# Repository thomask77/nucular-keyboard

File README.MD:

Toolchain
=========
  * gcc-arm-embedded toolchain >= 4.9-2014-q4
    * https://launchpad.net/gcc-arm-embedded

  * Other tools (use cygwin for windows)
    * python2
    * make

  * Initial flash programming
    * STM32 ST-LINK utility (windows)
    * https://github.com/texane/stlink (linux)

  * Flash programming with DFU bootloader
    * STM32 DfuSe utility (windows)
    * Openmoko dfu-util (linux)

Building
========
```bash
make boot    # Build USB DFU bootloader
make all     # Build actual keyboard application
```

Initial flash programming
=========================
Unfortunately, the STM32L052 does not have a built-in USB bootloader. So the
initial programming has to be done using a SWD adapter. A cheap STM32 discovery
board will do fine.

Windows
-------
Use the ST-LINK utility to flash `obj_boot/f00b00t.hex` and
`obj_app/nucular_kb.hex`.
   
Hint: You can also copy the ST-LINK utility to Tools/st-link and use `make`
to do the flashing:

```bash
make boot_flash
make flash
```

Linux
-----
Use Texane's stlink utility to do the flashing:

```bash
sudo st-flash --reset write obj_boot/f00b00t.bin 0x08000000
sudo st-flash --reset write obj_app/drquad.bin 0x08010000
```

Hint: Read the st-flash documentation and install udev rules
to flash without root privileges.

Flash programming with DFU bootloader
=====================================
After the USB DFU bootloader has been flashed, the application can be updated
without any external tools. Press FN+POWER on your keyboard to enter the DFU-
bootloader mode.

Windows
-------
Use ST's DfuSe Application to flash `obj_app/nucular_kb.dfu`

Linux
-----
Use Openmoko's dfu-util to flash the application:

```bash
sudo dfu-util -D obj_app/nucular_kb.dfu
```

printf()-Debugging
==================
The application uses a generic HID endpoint to print debug messages. This
endpoint is fully compatible with PJRC's [hid_listen] 
(https://www.pjrc.com/teensy/hid_listen.html) program.

The program (source and binaries) is included in the Tools directory.

Eclipse settings
================
  * Download and configure Eclipse Luna:
    * Help -> Install new Software -> Add
      * Name: `http://pydev.org/updates`
      * Location: `http://pydev.org/updates`
    * Install the following plugins:
      * Programming Languages
        * C/C++ Development Tools
      * Mobile and Device Development
        * C/C++ GCC Cross Compiler Support
        * C/C++ GDB Hardware Debugging
     * PyDev
        * PyDev for Eclipse
      * Collaboration
        * Eclipse Git Team Provider

  * Window -> Preferences
    * C/C++
      * Build -> Console -> Limit console output: `5000`
      * Editor -> Scalability -> .. number of lines: `50000`
      * Editor -> Folding -> Enable folding of preprocessor branches
      * Code Style -> Formatter -> Import: `Docs/Codestyle.xml`
      * Code Analysis -> Uncheck all options
    * General -> Editors -> Text Editors -> Spelling -> Disable spell checking

Import Project
--------------
  * File -> New -> Makefile Project with Existing Code
    -> Toolchain for Indexer Settigns: Cross GCC

  * Project -> Uncheck "Build Automatically" 
  
  * Project -> Properties -> C/C++ General
    * Preprocessor Include Paths, Macros, etc. -> Providers
      * CDT GCC Build Output Parser: `arm-none-eabi-gcc`
      * CDT Cross GCC Built-in Compiler Settings: `arm-none-eabi-gcc -E -P -v -dD "${INPUTS}"`

  * Make Target Window, Right Click -> New...
    * Target-name: `all -j8`
    * Target-name: `clean`

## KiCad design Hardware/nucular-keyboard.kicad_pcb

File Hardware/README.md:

**KICAD BRANCH -- WORK IN PROGRESS**

**EXPECT FREQUENT REBASES**

# Hardware

# Software

  * KiCad nightly
  * FreeCAD v0.17_pre

# Credits
  * 3D Models for AA01B-S040VA1 and T60 Keyboard by Cong Nguyen, Licensed under
    [CC-BY](http://creativecommons.org/licenses/by/4.0/) License:
    * https://grabcad.com/library/aa01b-s040va1-model-1
    * https://grabcad.com/library/thinkpad-t60-keyboard-with-trackpoint-1

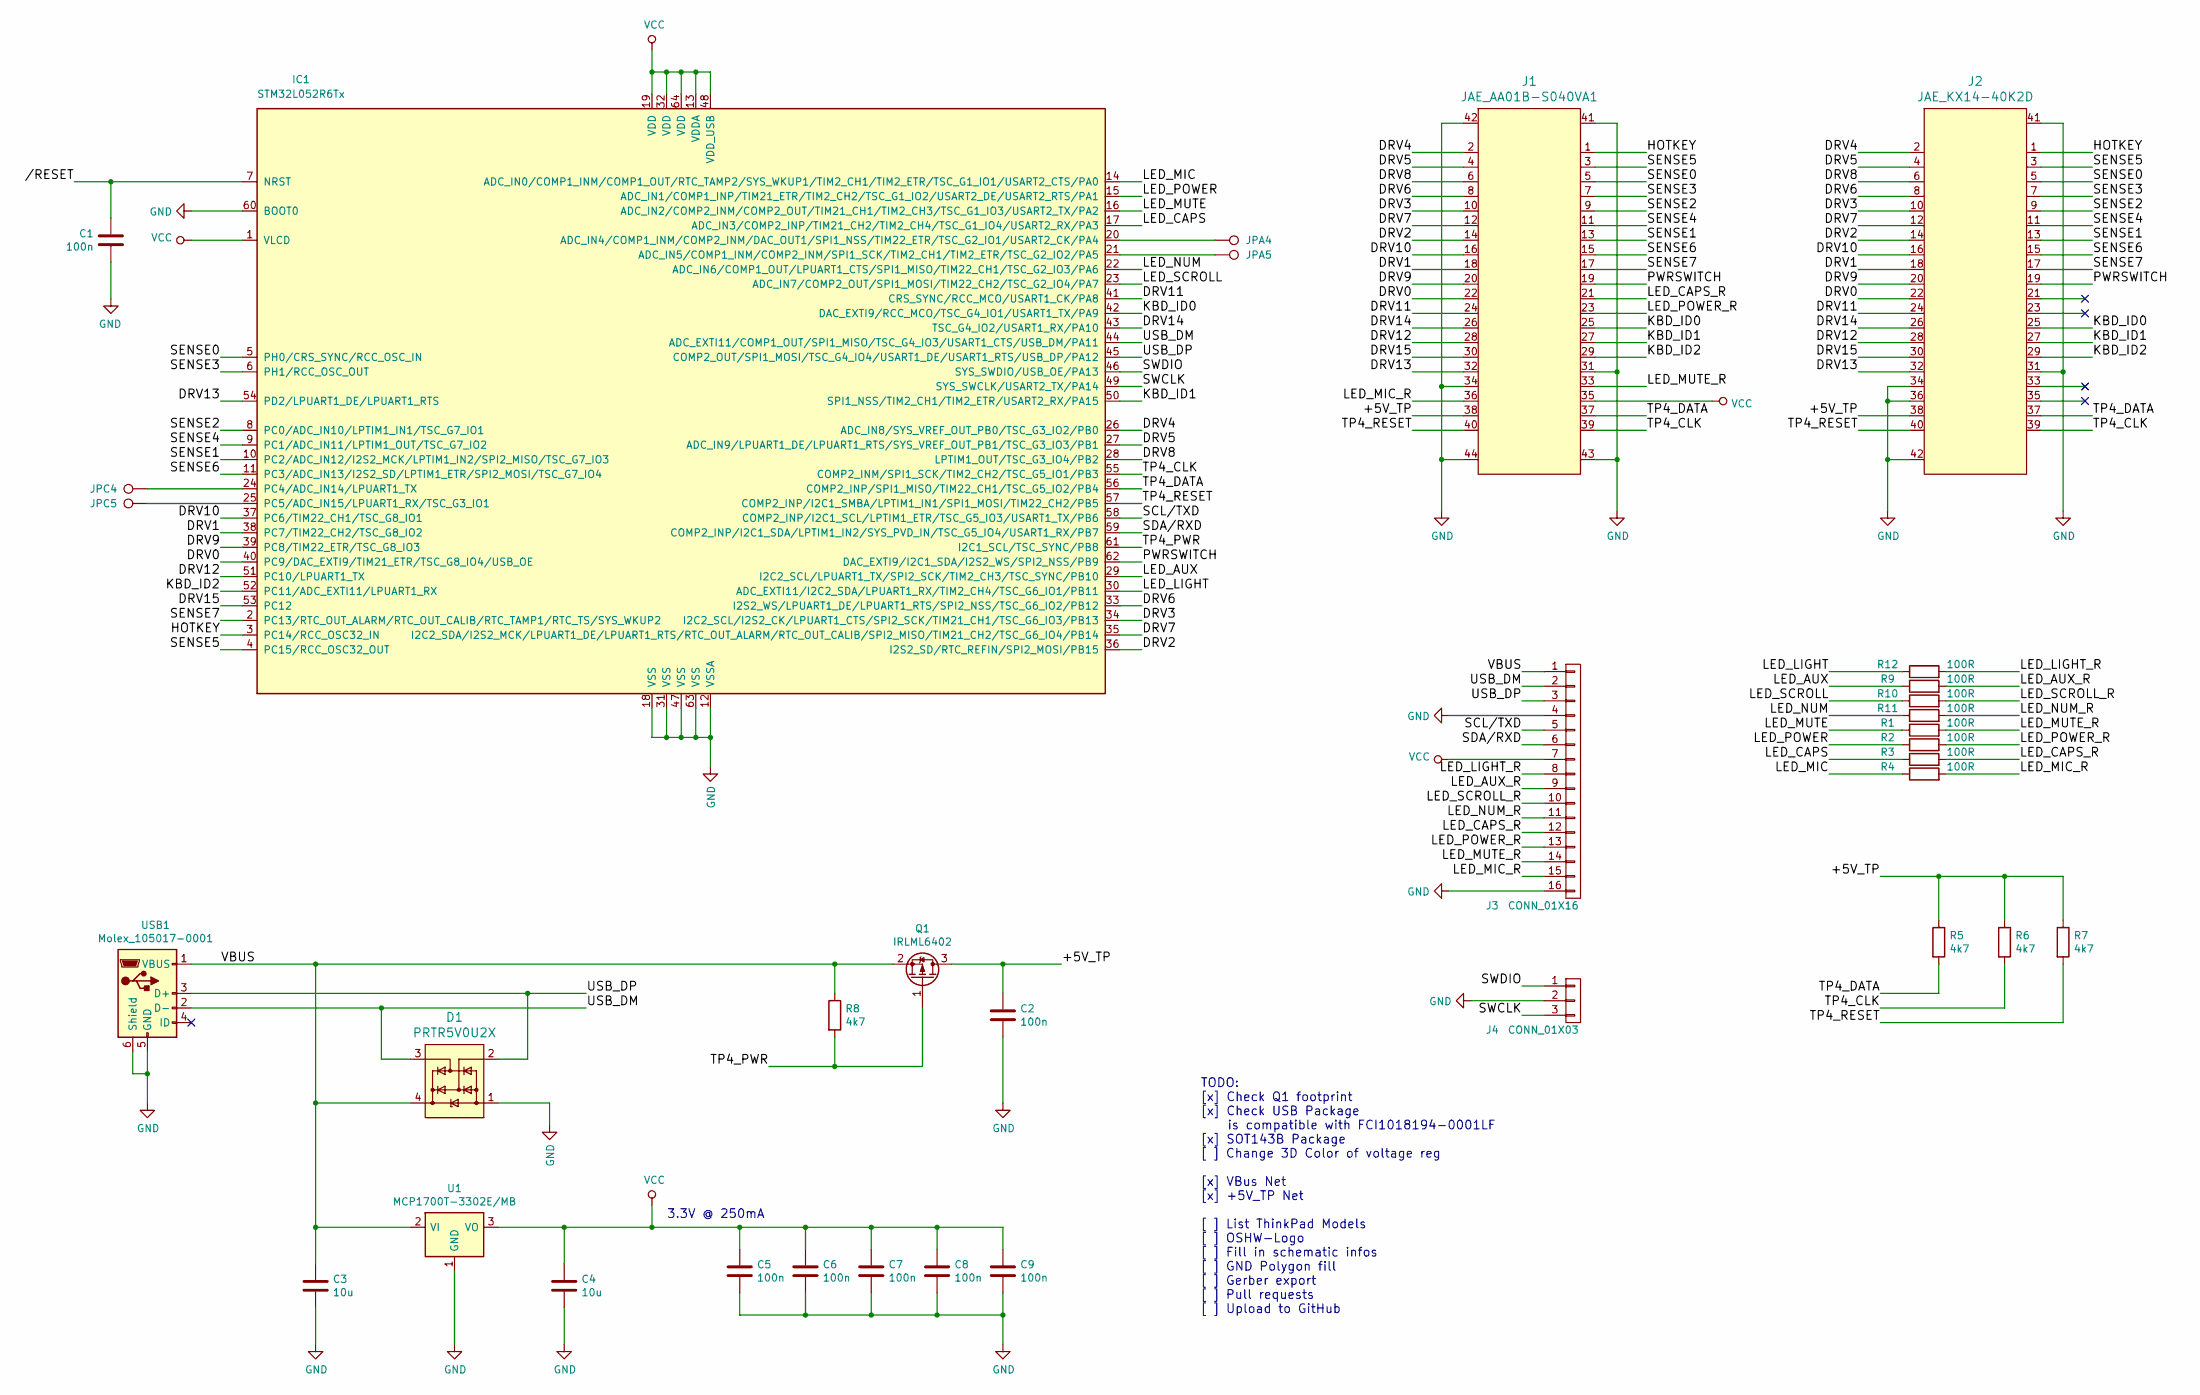
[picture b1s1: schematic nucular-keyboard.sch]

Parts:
C1, C2, C5, C6, C7, C8, C9: 100n; C_0402
C3, C4: 10u; C_0603
D1: PRTR5V0U2X; SOT143B
IC1: STM32L052R6Tx; LQFP-64_10x10mm_Pitch0.5mm
J1: JAE_AA01B-S040VA1
J2: JAE_KX14-40K2D
J3: CONN_01X16; Pin_Header_Straight_1x16_Pitch2.54mm
J4: CONN_01X03; Pin_Header_Straight_1x03_Pitch2.54mm
JPA4, JPA5: TEST_1P; SolderWirePad_single_0-8mmDrill
JPC4, JPC5: TEST_1P; SolderWirePad_single_0-8mmDrill
Q1: IRLML6402; SOT-23
R1, R2, R3, R4, R9, R10, R11, R12: 100R; R_0402
R5, R6, R7, R8: 4k7; R_0402
U1: MCP1700T-3302E/MB; SOT89-3
USB1: Molex_105017-0001; Molex_105017-0001_USB-Micro-B

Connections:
/+5V_TP: C2.1, J1.38, J2.38, Q1.3 (D), R5.1, R6.1, R7.1
//RESET: C1.1, IC1.7 (NRST)
/DRV0: IC1.40 (PC9/DAC_EXTI9/TIM21_ETR/TSC_G8_IO4/USB_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), J1.22, J2.22
/DRV1: IC1.38 (PC7/TIM22_CH2/TSC_G8_IO2), J1.18, J2.18
/DRV2: IC1.36 (I2S2_SD/RTC_REFIN/SPI2_MOSI/PB15), J1.14, J2.14
/DRV3: IC1.34 (I2C2_SCL/I2S2_CK/LPUART1_CTS/SPI2_SCK/T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), J1.10, J2.10
/DRV4: IC1.26 (ADC_IN8/SYS_VREF_OUT_PB0/TSC_G3_IO2/PB0), J1.2, J2.2
/DRV5: IC1.27 (ADC_IN9/LPUART1_DE/LPUART1_RTS/SYS_VREF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), J1.4, J2.4
/DRV6: IC1.33 (I2S2_WS/LPUART1_DE/LPUART1_RTS/SPI2_NSS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), J1.8, J2.8
/DRV7: IC1.35 (I2C2_SDA/I2S2_MCK/LPUART1_DE/LPUART1_RT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), J1.12, J2.12
/DRV8: IC1.28 (LPTIM1_OUT/TSC_G3_IO4/PB2), J1.6, J2.6
/DRV9: IC1.39 (PC8/TIM22_ETR/TSC_G8_IO3), J1.20, J2.20
/DRV10: IC1.37 (PC6/TIM22_CH1/TSC_G8_IO1), J1.16, J2.16
/DRV11: IC1.41 (CRS_SYNC/RCC_MCO/USART1_CK/PA8), J1.24, J2.24
/DRV12: IC1.51 (PC10/LPUART1_TX), J1.28, J2.28
/DRV13: IC1.54 (PD2/LPUART1_DE/LPUART1_RTS), J1.32, J2.32
/DRV14: IC1.43 (TSC_G4_IO2/USART1_RX/PA10), J1.26, J2.26
/DRV15: IC1.53 (PC12), J1.30, J2.30
/HOTKEY: IC1.3 (PC14/RCC_OSC32_IN), J1.1, J2.1
/KBD_ID0: IC1.42 (DAC_EXTI9/RCC_MCO/TSC_G4_IO1/USART1_TX/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), J1.25, J2.25
/KBD_ID1: IC1.50 (SPI1_NSS/TIM2_CH1/TIM2_ETR/USART2_RX/PA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), J1.27, J2.27
/KBD_ID2: IC1.52 (PC11/ADC_EXTI11/LPUART1_RX), J1.29, J2.29
/LED_AUX: IC1.29 (I2C2_SCL/LPUART1_TX/SPI2_SCK/TIM2_CH3/T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), R9.1
/LED_AUX_R: J3.9, R9.2
/LED_CAPS: IC1.17 (ADC_IN3/COMP2_INP/TIM21_CH2/TIM2_CH4/TS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), R3.1
/LED_CAPS_R: J1.21, J3.12, R3.2
/LED_LIGHT: IC1.30 (ADC_EXTI11/I2C2_SDA/LPUART1_RX/TIM2_CH4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), R12.1
/LED_LIGHT_R: J3.8, R12.2
/LED_MIC: IC1.14 (ADC_IN0/COMP1_INM/COMP1_OUT/RTC_TAMP2/S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), R4.1
/LED_MIC_R: J1.36, J3.15, R4.2
/LED_MUTE: IC1.16 (ADC_IN2/COMP2_INM/COMP2_OUT/TIM21_CH1/T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), R1.1
/LED_MUTE_R: J1.33, J3.14, R1.2
/LED_NUM: IC1.22 (ADC_IN6/COMP1_OUT/LPUART1_CTS/SPI1_MISO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), R11.1
/LED_NUM_R: J3.11, R11.2
/LED_POWER: IC1.15 (ADC_IN1/COMP1_INP/TIM21_ETR/TIM2_CH2/TS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), R2.1
/LED_POWER_R: J1.23, J3.13, R2.2
/LED_SCROLL: IC1.23 (ADC_IN7/COMP2_OUT/SPI1_MOSI/TIM22_CH2/T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), R10.1
/LED_SCROLL_R: J3.10, R10.2
/PWRSWITCH: IC1.62 (DAC_EXTI9/I2C1_SDA/I2S2_WS/SPI2_NSS/PB9), J1.19, J2.19
/SCL/TXD: IC1.58 (COMP2_INP/I2C1_SCL/LPTIM1_ETR/TSC_G5_IO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), J3.5
/SDA/RXD: IC1.59 (COMP2_INP/I2C1_SDA/LPTIM1_IN2/SYS_PVD_I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), J3.6
/SENSE0: IC1.5 (PH0/CRS_SYNC/RCC_OSC_IN), J1.5, J2.5
/SENSE1: IC1.10 (PC2/ADC_IN12/I2S2_MCK/LPTIM1_IN2/SPI2_M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), J1.13, J2.13
/SENSE2: IC1.8 (PC0/ADC_IN10/LPTIM1_IN1/TSC_G7_IO1), J1.9, J2.9
/SENSE3: IC1.6 (PH1/RCC_OSC_OUT), J1.7, J2.7
/SENSE4: IC1.9 (PC1/ADC_IN11/LPTIM1_OUT/TSC_G7_IO2), J1.11, J2.11
/SENSE5: IC1.4 (PC15/RCC_OSC32_OUT), J1.3, J2.3
/SENSE6: IC1.11 (PC3/ADC_IN13/I2S2_SD/LPTIM1_ETR/SPI2_MO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), J1.15, J2.15
/SENSE7: IC1.2 (PC13/RTC_OUT_ALARM/RTC_OUT_CALIB/RTC_TA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), J1.17, J2.17
/SWCLK: IC1.49 (SYS_SWCLK/USART2_TX/PA14), J4.3
/SWDIO: IC1.46 (SYS_SWDIO/USB_OE/PA13), J4.1
/TP4_CLK: IC1.55 (COMP2_INM/SPI1_SCK/TIM2_CH2/TSC_G5_IO1/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), J1.39, J2.39, R6.2
/TP4_DATA: IC1.56 (COMP2_INP/SPI1_MISO/TIM22_CH1/TSC_G5_IO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), J1.37, J2.37, R5.2
/TP4_PWR: IC1.61 (I2C1_SCL/TSC_SYNC/PB8), Q1.1 (G), R8.2
/TP4_RESET: IC1.57 (COMP2_INP/I2C1_SMBA/LPTIM1_IN1/SPI1_MOS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), J1.40, J2.40, R7.2
/USB_DM: D1.3 (DM), IC1.44 (ADC_EXTI11/COMP1_OUT/SPI1_MISO/TSC_G4_I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), J3.2, USB1.2 (D-)
/USB_DP: D1.2 (DP), IC1.45 (COMP2_OUT/SPI1_MOSI/TSC_G4_IO4/USART1_D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), J3.3, USB1.3 (D+)
/VBUS: C3.1, D1.4 (VBUS), J3.1, Q1.2 (S), R8.1, U1.2 (VI), USB1.1 (VBUS)
GND: C1.2, C2.2, C3.2, C4.2, C5.2, C6.2, C7.2, C8.2, C9.2, D1.1 (GND), IC1.12 (VSSA), IC1.18 (VSS), IC1.31 (VSS), IC1.47 (VSS), IC1.60 (BOOT0), IC1.63 (VSS), J1.31, J1.34, J1.41, J1.42, J1.43, J1.44, J2.31, J2.34, J2.36, J2.41, J2.42, J3.4, J3.16, J4.2, U1.1 (GND), USB1.5 (GND), USB1.6 (Shield)
unnamed: IC1.20 (ADC_IN4/COMP1_INM/COMP2_INM/DAC_OUT1/SP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), JPA4.1
unnamed: IC1.21 (ADC_IN5/COMP1_INM/COMP2_INM/SPI1_SCK/TI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), JPA5.1
unnamed: IC1.24 (PC4/ADC_IN14/LPUART1_TX), JPC4.1
unnamed: IC1.25 (PC5/ADC_IN15/LPUART1_RX/TSC_G3_IO1), JPC5.1
VCC: C4.1, C5.1, C6.1, C7.1, C8.1, C9.1, IC1.1 (VLCD), IC1.13 (VDDA), IC1.19 (VDD), IC1.32 (VDD), IC1.48 (VDD_USB), IC1.64 (VDD), J1.35, J3.7, U1.3 (VO)

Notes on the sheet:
3.3V @ 250mA
TODO: [x] Check Q1 footprint [x] Check USB Package is compatible with FCI1018194-0001LF [x] SOT143B Package [ ] Change 3D Color of voltage reg [x] VBus Net [x] +5V_TP Net [ ] List ThinkPad Models [ ] OSHW-Logo [ ] Fill in schematic infos [ ] GND Polygon fill [ ] Gerber export [ ] Pull requests [ ] 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

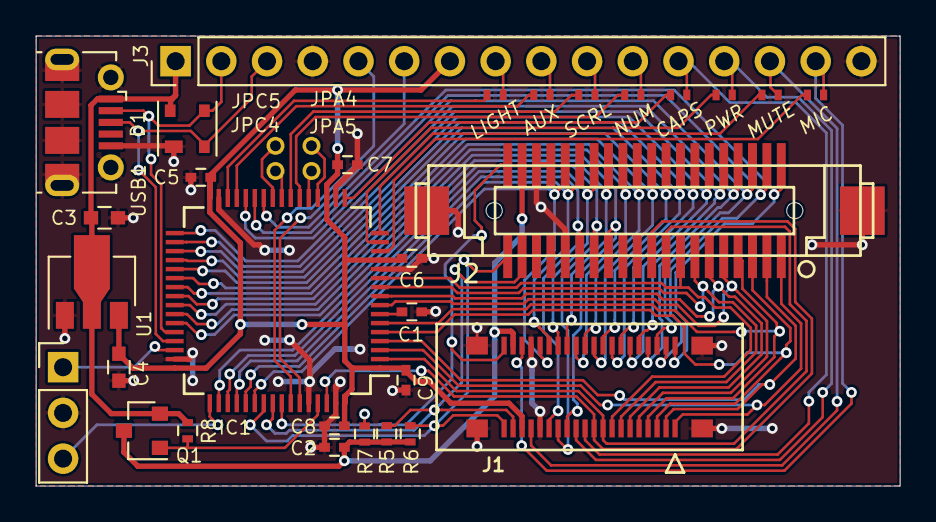
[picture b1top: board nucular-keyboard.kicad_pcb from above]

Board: 2 copper layers, 48.0 x 25.0 mm, 34 parts (0 on the bottom side), 64 nets.

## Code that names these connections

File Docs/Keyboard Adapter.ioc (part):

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Mcu.Name=STM32L052R(6-8)Tx
Mcu.Package=LQFP64
Mcu.UserName=STM32L052R8Tx
PA0-WKUP.Signal=S_TIM2_CH1
PA1.Signal=S_TIM2_CH2
PA11.Mode=Device
PA11.Signal=USB_DM
PA12.Mode=Device
PA12.Signal=USB_DP
PA13.Mode=Serial_Wire
PA13.Signal=SYS_SWDIO
PA14.Mode=Serial_Wire
PA14.Signal=SYS_SWCLK
PA2.Signal=S_TIM21_CH1
PA3.Signal=S_TIM21_CH2
PA6.Signal=S_TIM22_CH1
PA7.Signal=S_TIM22_CH2
PB10.Signal=S_TIM2_CH3
PB11.Signal=S_TIM2_CH4
PB6.GPIOParameters=GPIO_Speed,GPIO_PuPd,GPIO_Mode
PB6.GPIO_Mode=GPIO_MODE_AF_PP
PB6.GPIO_PuPd=GPIO_PULLUP
PB6.GPIO_Speed=GPIO_SPEED_LOW
PB6.Mode=Asynchronous
PB6.Signal=USART1_TX
PB7.GPIOParameters=GPIO_Speed,GPIO_PuPd,GPIO_Mode
PB7.GPIO_Mode=GPIO_MODE_AF_PP
PB7.GPIO_PuPd=GPIO_PULLUP
PB7.GPIO_Speed=GPIO_SPEED_LOW
PB7.Mode=Asynchronous
PB7.Signal=USART1_RX
RCC.HSE_VALUE=8000000
RCC.SYSCLKSource=RCC_SYSCLKSOURCE_PLLCLK

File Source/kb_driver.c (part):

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{
    int pwm = gamma_tab[level];

    TIM2->CCR1  = pwm;  // PA0    LED_MIC
    TIM2->CCR2  = pwm;  // PA1    LED_POWER
    TIM21->CCR1 = pwm;  // PA2    LED_MUTE
    TIM21->CCR2 = pwm;  // PA3    LED_CAPS
    TIM22->CCR1 = pwm;  // PA6    LED_NUM
    TIM22->CCR2 = pwm;  // PA7    LED_SCROLL
    TIM2->CCR3  = pwm;  // PB10   LED_AUX
}


void kb_set_thinklight(uint8_t level)
{
    int pwm = gamma_tab[level];
    TIM2->CCR4  = pwm;  // PB11   LED_LIGHT
}


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
    // Initialize LED PWM outputs
    //
    // PA0      TIM2_CH1    LED_MIC
    // PA1      TIM2_CH2    LED_POWER
    // PB10     TIM2_CH3    LED_AUX
    // PB11     TIM2_CH4    LED_LIGHT
    // PA2      TIM21_CH1   LED_MUTE
    // PA3      TIM21_CH2   LED_CAPS
    // PA6      TIM22_CH1   LED_NUM
    // PA7      TIM22_CH2   LED_SCROLL
    //
    RCC->APB1ENR |= RCC_APB1ENR_TIM2EN;
    RCC->APB2ENR |= RCC_APB2ENR_TIM21EN;
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
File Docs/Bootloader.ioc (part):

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Mcu.Name=STM32L052R(6-8)Tx
Mcu.Package=LQFP64
Mcu.UserName=STM32L052R8Tx
PA11.Mode=Device
PA11.Signal=USB_DM
PA12.Mode=Device
PA12.Signal=USB_DP
PA13.Mode=Serial_Wire
PA13.Signal=SYS_SWDIO
PA14.Mode=Serial_Wire
PA14.Signal=SYS_SWCLK
PB9.GPIOParameters=GPIO_Label,GPIO_PuPd,GPIO_Mode
PB9.GPIO_Label=PWRSWITCH
PB9.GPIO_Mode=GPIO_MODE_INPUT
PB9.GPIO_PuPd=GPIO_PULLUP
PB9.Signal=GPIO_Input
PC14-OSC32_IN.GPIOParameters=GPIO_Label,GPIO_PuPd,GPIO_Mode
PC14-OSC32_IN.GPIO_Label=HOTKEY
PC14-OSC32_IN.GPIO_Mode=GPIO_MODE_INPUT
PC14-OSC32_IN.GPIO_PuPd=GPIO_PULLUP
PC14-OSC32_IN.Signal=GPIO_Input
RCC.HSE_VALUE=8000000
RCC.SYSCLKSource=RCC_SYSCLKSOURCE_PLLCLK

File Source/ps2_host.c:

/**
 * Nucular Keyboard - PS/2 host controller functions
 * Copyright (C)2015 Thomas Kindler <mail_nucular@t-kindler.de>
 *
 * This program is free software: you can redistribute it and/or modify
 * it under the terms of the GNU General Public License as published by
 * the Free Software Foundation, either version 3 of the License, or
 * (at your option) any later version.
 *
 * This program is distributed in the hope that it will be useful,
 * but WITHOUT ANY WARRANTY; without even the implied warranty of
 * MERCHANTABILITY or FITNESS FOR A PARTICULAR PURPOSE.  See the
 * GNU General Public License for more details.
 *
 * You should have received a copy of the GNU General Public License
 * along with this program.  If not, see <http://www.gnu.org/licenses/>.
 */

/*
     see http://www.computer-engineering.org/ps2protocol/
     see https://github.com/tmk/tmk_keyboard
     TODO: receive/send buffer
     TODO: inhibit on overflow
     TODO: handle time outs
*/

#include "ps2_host.h"
#include "ustime.h"
#include "stm32l0xx_hal.h"
#include <stdbool.h>

#define PIN_CLK     GPIO_PIN_3
#define PIN_DATA    GPIO_PIN_4

// PS/2 Receive state
//
static volatile int rx_frame;
static volatile int rx_frame_pos;

/*static*/ volatile int rx_buf = -1;

static volatile int rx_bytes;
static volatile int rx_errors;

// PS/2 Transmit state
//
static volatile int tx_frame;
static volatile int tx_frame_pos;

static volatile int tx_buf = -1;


volatile bool foo;


static bool check_frame(int frame)
{
    if (frame & (1<<0))         // start bit
        return false;

    if (!(frame & (1<<10)))     // stop bit
        return false;

    int parity = 0;             // parity check
    for (int b=1; b<=9; b++)
        parity ^= !!(frame & (1 << b));

    if (parity != 1)
        return false;

    return true;
}


static void handle_clk_edge(int data)
{
    if (rx_frame_pos == 0 && data != 0) {
        // invalid start bit.. try to resync
        //
        return;
    }

    // add bit to receive register
    //
    rx_frame |= !!data << rx_frame_pos++;

    if (rx_frame_pos >= 11) {
        // start + 8 bits + parity + stop received
        //
        if (check_frame(rx_frame)) {
            rx_buf = (rx_frame >> 1) & 255;

            GPIOB->BRR = PIN_CLK;   // Inhibit clock
            rx_bytes++;
        }
        else {
            rx_errors++;
        }

        rx_frame = 0;
        rx_frame_pos = 0;
    }
}


void EXTI2_3_IRQHandler(void)
{
    uint32_t exti_pr = EXTI->PR;

    if (exti_pr & EXTI_PR_PR3) {
        if (!foo)
            handle_clk_edge(GPIOB->IDR & PIN_DATA);
    }

    EXTI->PR = exti_pr;     // clear interrupts
    EXTI->PR;               // dummy read to avoid glitches
}


static void ps2_send_byte(uint8_t data)
{
    int parity = 0;
    for (int b=0; b<=7; b++)
        parity ^= !!(data & (1 << b));

    // start + data + parity + stop
    //
    int frame = (data << 1) | (!parity << 9) | (1 << 10);

    foo = 1;

    GPIOB->BSRR = (PIN_CLK << 16);  // clk lo
    delay_us(100);

    for (int i=0; i<11; i++) {
        if (frame & (1<<i))
            GPIOB->BSRR = PIN_DATA;
        else
            GPIOB->BRR = PIN_DATA;

        delay_us(15);

        GPIOB->BSRR = PIN_CLK;  // clk hi

        while (!(GPIOB->IDR & PIN_CLK));
        while (GPIOB->IDR & PIN_CLK);
    }

    foo = 0;
}


ssize_t ps2_read(void *buf, size_t n)
{
    uint8_t *d = buf;

    for (int i=0; i<n; i++) {
        while (rx_buf == -1);
        *d++ = rx_buf;

        rx_buf = -1;
        GPIOB->BSRR = PIN_CLK;   // Idle
    }

    return n;
}


ssize_t ps2_write(const void *buf, size_t n)
{
    const char *s = buf;

    for (int i=0; i<n; i++)
        ps2_send_byte(*s++);

    return n;
}


void ps2_init(void)
{
    // PB3      TP4_CLK
    // PB4      TP4_DATA
    //
    GPIOB->BSRR = GPIO_PIN_3;   // Idle
    GPIOB->BSRR = GPIO_PIN_4;   // Idle

    // Set up EXTI3 Interrupt.. dämliche HAL-Library.
    // EXTI und OUTPUT_OD gleichzeitig geht nicht mehr m(
    //
    HAL_GPIO_Init(GPIOB, &(GPIO_InitTypeDef) {
        .Pin   = GPIO_PIN_3,
        .Mode  = GPIO_MODE_IT_FALLING,
    } );

    HAL_GPIO_Init(GPIOB, &(GPIO_InitTypeDef) {
        .Pin   = GPIO_PIN_4 | GPIO_PIN_3,
        .Mode  = GPIO_MODE_OUTPUT_OD,
        .Pull  = GPIO_PULLUP,
        .Speed = GPIO_SPEED_LOW
    } );

    NVIC_SetPriority(EXTI2_3_IRQn, 15);
    NVIC_EnableIRQ(EXTI2_3_IRQn);
}

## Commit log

2015-01-11 Initial import from a private repo
2015-01-14 Updated copyright headers
2015-01-25 Added some documentation photos
2015-01-28 Official USB PID 0x60c0 from OpenMoko. Thanks Harald!
2015-02-01 Added ThinkLight buttons: FN + PgUp increases brightness FN + PgDn decreases brightness
2015-02-28 ThinkLight with smooth steps
2015-03-17 Explicitly use python 2.x in scripts
2015-03-17 Improved documentation
2015-05-27 Added left Windows-Key for FRU 42T3946 and similar keyboards. Thanks Jakob!
2017-04-30 3D Model for JAE-KX14-40-K2D receptacle
2017-04-30 3D Model for JAE-AA01B-S040VA1 receptacle
2017-04-30 added readme
2017-04-30 gitignore
2017-04-30 first layout version
2017-04-30 some libraries
2017-05-01 more footprint and library stuff
2017-05-02 Corrected footprint
2017-05-02 Big clean-up
2017-05-03 Renamed libray to 000-xxx, so it's always on top
2017-05-07 fill polys
2017-05-19 plane layers
2017-05-19 finish?
